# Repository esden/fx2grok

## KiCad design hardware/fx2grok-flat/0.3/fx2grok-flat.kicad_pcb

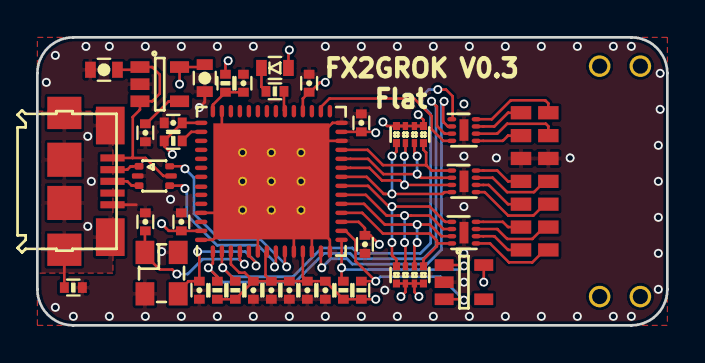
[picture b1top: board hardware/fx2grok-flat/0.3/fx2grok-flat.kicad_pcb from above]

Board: 4 copper layers, 35.0 x 16.0 mm, 37 parts (0 on the bottom side), 41 nets.

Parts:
C1, C2, C3, C4, C5, C6, C9, C10: 100n; C_0402
C7, C8: 2u2; C_0402
C11, C13: 4u7; C_0603
C12: 10n; C_0402
C14: 1u; C_0402
C15, C16: 10p; C_0402
D1: GRN; D_0603
IC1: CY7C68013A-56; QFN-56-1EP_8x8mm_Pitch0.5mm
J1: Conn; TFM-107-02-x-DH
P1: pkl_USB_OTG; Connector_USB_Micro_B_SMD
R1, R2, R3, R4: 2k7; R_0402
R5, R6, R7: 100k; R_0402
R8, R9: 100k; R_Array_Convex_4x0402
R10: 1m; R_0402
U1: 3.3V; SOT-23-5
U2: USBLC6-2; SOT-666
U3, U4, U6: IP425x-4-TTL; DFN-8-1EP_1.35x1.7mm_Pitch0.4mm
U5: 24LC00; SOT-23-5
X1: 24MHz; ABM8

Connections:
+3V3: C1.1, C2.1, C3.1, C4.1, C5.1, C6.1, C7.1, C8.1, C9.1, C10.1, C13.1, D1.A, IC1.3, IC1.7, IC1.11, IC1.17, IC1.27, IC1.32, IC1.43, IC1.55, R2.2, R3.2, R4.2, R5.2, R6.1, R7.1, R8.2, R8.4, R8.6, R8.8, R9.2, R9.4, R9.6, R9.8, U1.5, U5.5
+5V: C11.1, P1.1, U1.1, U1.3, U2.5
/CLK: IC1.30, U6.4
/IFCLK: IC1.13, U6.2
/PA1: IC1.34, R1.2
/PB0: IC1.18, R8.1, U3.4
/PB1: IC1.19, R8.3, U3.3
/PB2: IC1.20, R8.5, U3.2
/PB3: IC1.21, R8.7, U3.1
/PB4: IC1.22, R9.1, U4.4
/PB5: IC1.23, R9.3, U4.3
/PB6: IC1.24, R9.5, U4.2
/PB7: IC1.25, R9.7, U4.1
/SCL: IC1.15, R2.1, U5.1
/SDA: IC1.16, R3.1, U5.3
/TRIG: IC1.1, R6.2, U6.3
/TRIG2: IC1.2, R7.2, U6.1
/USBD_N: IC1.9, U2.6
/USBD_P: IC1.8, U2.4
/WAKEUP: IC1.44, R5.1
/XTALIN: C16.1, IC1.5, X1.2
/XTALOUT: C15.1, IC1.4, X1.1
/shield: P1.GND, R10.1
/xCLK: J1.12, U6.5
/xIFCLK: J1.14, U6.7
/xPB0: J1.1, U3.5
/xPB1: J1.2, U3.6
/xPB2: J1.3, U3.7
/xPB3: J1.4, U3.8
/xPB4: J1.5, U4.5
/xPB5: J1.6, U4.6
/xPB6: J1.7, U4.7
/xPB7: J1.8, U4.8
/xTRIG: J1.11, U6.6
/xTRIG2: J1.13, U6.8
/xUSBD_N: P1.2, U2.1
/xUSBD_P: P1.3, U2.3
/~RESET: C14.1, IC1.42, R4.1
GND: C1.2, C2.2, C3.2, C4.2, C5.2, C6.2, C7.2, C8.2, C9.2, C10.2, C11.2, C12.2, C13.2, C14.2, C15.2, C16.2, IC1.6, IC1.10, IC1.12, IC1.14, IC1.26, IC1.28, IC1.41, IC1.53, IC1.56, IC1.57, J1.9, J1.10, P1.5, R10.2, U1.2, U2.2, U3.9, U4.9, U5.2, U6.9, X1.GND
unnamed: C12.1, U1.4
unnamed: D1.C, R1.1

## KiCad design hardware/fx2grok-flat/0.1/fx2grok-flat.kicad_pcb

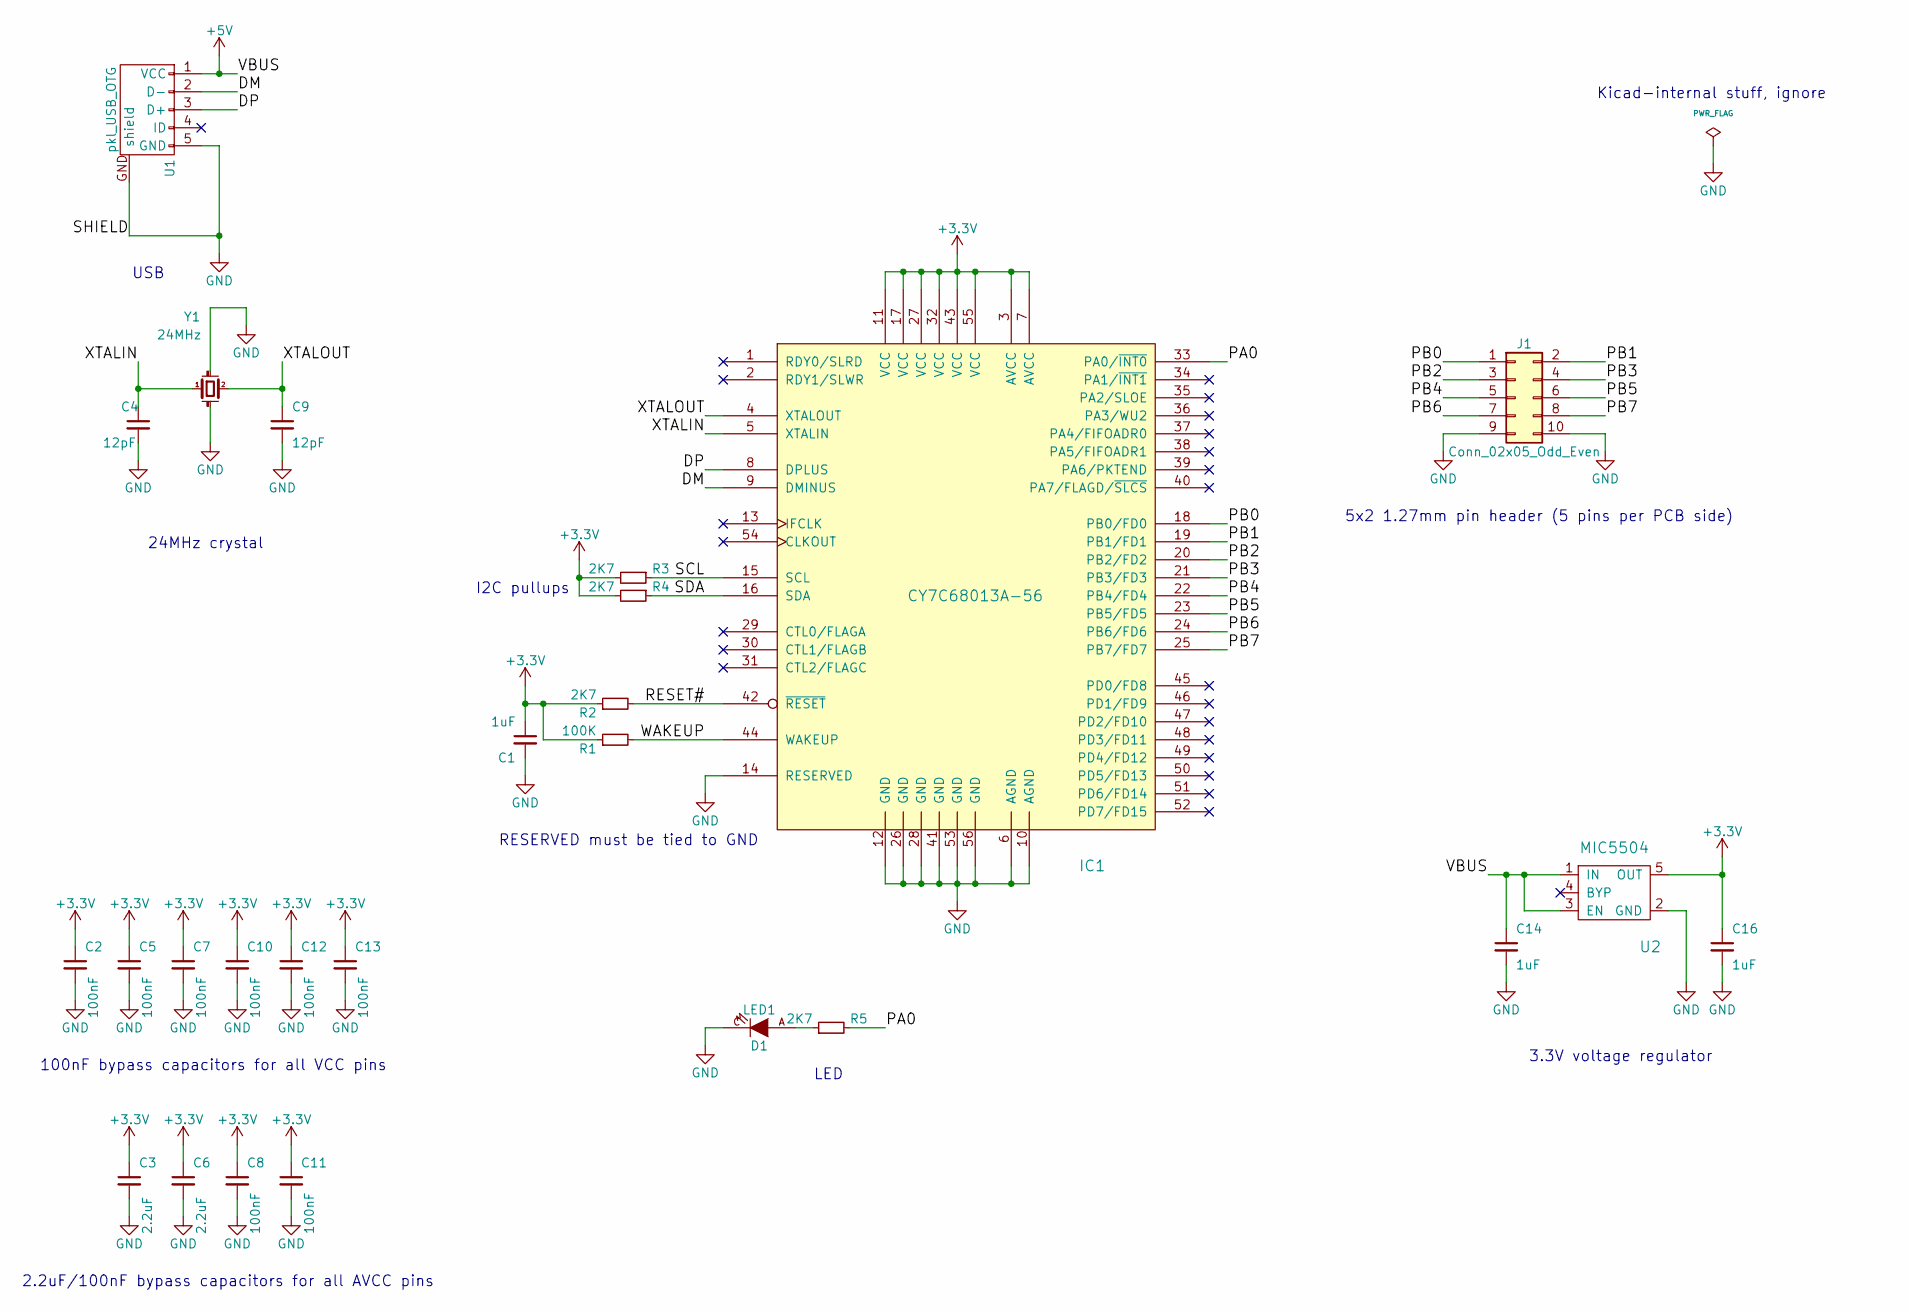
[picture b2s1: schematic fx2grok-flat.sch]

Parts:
C1, C14, C16: 1uF; C_0402
C2, C5, C7, C8, C10, C11, C12, C13: 100nF; C_0402
C3, C6: 2.2uF; C_0402
C4, C9: 12pF; C_0402
D1: LED1; D_0603
IC1: CY7C68013A-56; QFN-56-1EP_8x8mm_Pitch0.5mm
J1: Conn_02x05_Odd_Even; FTSH-105-XX-X-DV
R1: 100K; R_0402
R2, R3, R4, R5: 2K7; R_0402
U1: pkl_USB_OTG; Connector_USB_Micro_B_SMD
U2: MIC5504; SOT-23-5
Y1: 24MHz; ABM8

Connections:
+3V3: C1.1, C2.1, C3.1, C5.1, C6.1, C7.1, C8.1, C10.1, C11.1, C12.1, C13.1, C16.1, IC1.3 (AVCC), IC1.7 (AVCC), IC1.11 (VCC), IC1.17 (VCC), IC1.27 (VCC), IC1.32 (VCC), IC1.43 (VCC), IC1.55 (VCC), R1.1, R2.1, R3.2, R4.2, U2.5 (OUT)
+5V: C14.1, U1.1 (VCC), U2.1 (IN), U2.3 (EN)
/DM: IC1.9 (DMINUS), U1.2 (D-)
/DP: IC1.8 (DPLUS), U1.3 (D+)
/PA0: IC1.33 (PA0/~INT0), R5.2
/PB0: IC1.18 (PB0/FD0), J1.1
/PB1: IC1.19 (PB1/FD1), J1.2
/PB2: IC1.20 (PB2/FD2), J1.3
/PB3: IC1.21 (PB3/FD3), J1.4
/PB4: IC1.22 (PB4/FD4), J1.5
/PB5: IC1.23 (PB5/FD5), J1.6
/PB6: IC1.24 (PB6/FD6), J1.7
/PB7: IC1.25 (PB7/FD7), J1.8
/RESET#: IC1.42 (~RESET), R2.2
/SCL: IC1.15 (SCL), R3.1
/SDA: IC1.16 (SDA), R4.1
/WAKEUP: IC1.44 (WAKEUP), R1.2
/XTALIN: C4.1, IC1.5 (XTALIN), Y1.1
/XTALOUT: C9.1, IC1.4 (XTALOUT), Y1.2
GND: C1.2, C2.2, C3.2, C4.2, C5.2, C6.2, C7.2, C8.2, C9.2, C10.2, C11.2, C12.2, C13.2, C14.2, C16.2, D1.C, IC1.6 (AGND), IC1.10 (AGND), IC1.12 (GND), IC1.14 (RESERVED), IC1.26 (GND), IC1.28 (GND), IC1.41 (GND), IC1.53 (GND), IC1.56 (GND), J1.9, J1.10, U1.5 (GND), U1.GND (shield), U2.2 (GND), Y1.GND (case)
unnamed: D1.A, R5.1

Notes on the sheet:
5x2 1.27mm pin header (5 pins per PCB side)
Kicad-internal stuff, ignore
LED
24MHz crystal
3.3V voltage regulator
USB
RESERVED must be tied to GND
2.2uF/100nF bypass capacitors for all AVCC pins
100nF bypass capacitors for all VCC pins
I2C pullups

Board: 4 copper layers, 26 parts (0 on the bottom side), 21 nets, no tracks yet.

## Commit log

2017-09-23 fx2grok-tiny: Place "values" on silkscreen but hide by default.
    These can be enabled when needed to have a nice assembly helper
    view in the Kicad 3D viewer.
2017-09-23 fx2grok-tiny: Add a silkscreen circle for the FX2's pin 1.
2017-09-23 fx2grok-tiny: Add missing Y1 to silkscreen.
2017-09-23 fx2grok-tiny: Move all files into 0.1/ again after all.
2017-09-23 fx2grok-tiny: Add warnings that version 0.1 is broken.
2017-09-29 fx2grok-tiny: Fix incorrect FX2 footprint.
2017-09-29 fx2grok-tiny: Add initial 0.2 version.
    Almost identical to 0.1, only the metadata has been updated
    and the 0.1 being broken warnings are removed.
2017-09-29 fx2grok-tiny: Reroute PCB from scratch with various changes.
    - The previously incorrect FX2 footprint is fixed now.
    - The FX2's thermal pad is set to GND now.
    - The FX2 footprint now has a dot on the copper as well as on the
    silkscreen for pin 1.
    - The PCB is now 11x11mm (instead of 13x13mm).
    - The 1.27mm pin header connectors are shortened and the pinout changed.
2017-09-29 fx2grok-tiny: Add generated 0.2 Gerber files.
2017-12-16 fx2grok-tiny: Random cosmetic/silkscreen changes.
    These are mostly done for being able to generate nice 3D previews in
    KiCad that can be helpful for assembling the device.
2018-04-13 Cleaned up and grouped schematic sections.
2018-04-13 Added pretty-kicad-libs library submodule.
2018-04-13 Final cleanup before placing prototype order.
2018-04-13 Added eeprom and pullups on probe inputs. Started routing.
2018-04-13 Added BOM unique part keys and made a few minor adjustments.
2018-04-13 Updated PKL.
2018-04-13 FX2Grok-flat with new frontend first routing pass.
    This is the status of the design as included on esden KiCad LP.
2018-04-13 More cleanup of the board routing.
2018-04-13 Added gitignore for kicad backup and net files.
2018-04-13 Placement plan layout.
2018-04-13 Recreated original schematic + input protection.
2018-04-13 Initial commit of fx2grok-flat.
2018-04-13 Minor value adjustment.
2018-04-14 Initial commit of fx2grok-flat V0.3.
2018-04-14 Added 3d models to the board file.
2018-04-19 Moved config flash to clean up PB0 trace.
2018-04-19 Untangled the TRIG and IFCLK traces.
2018-04-19 Added TRIG2 (RDY1/SLWR) as per @StefanBruens request. :D
2018-04-19 Added via stitching around the board.
2018-04-19 Corrected board length. (was off by 0.1mm)
2018-04-19 Updated USB ESD diode network chip footprint.
2018-04-19 Added TRIG2 silkscreen designator.
2018-04-19 Added GND via and fixed a DRC error.
2018-04-19 Left a note that the next revision has to get roundrect pads.
    Totally forgot to change them... and I already ordered the boards so it
    is too late for the current revision. :(

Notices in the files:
hardware/fx2grok-flat/0.1/fx2grok-flat.kicad_pcb:
CC-BY-SA V4.0
hardware/fx2grok-flat/0.2/fx2grok-flat.sch:
(C) 2017 1BitSquared
(C) 2017 Piotr Esden-tempski
hardware/fx2grok-flat/0.3/fx2grok-flat.kicad_pcb:
CC-BY-SA 4.0
